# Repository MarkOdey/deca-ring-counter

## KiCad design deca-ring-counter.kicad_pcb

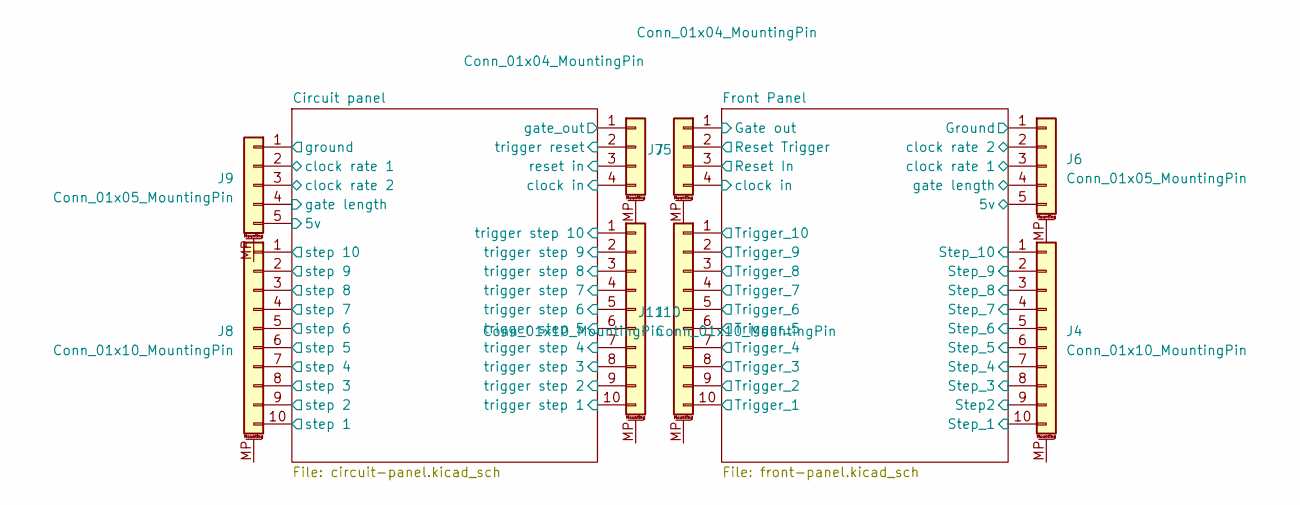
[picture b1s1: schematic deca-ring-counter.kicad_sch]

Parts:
J4, J11: Conn_01x10_MountingPin; PinHeader_1x10_P2.54mm_Vertical
J5: Conn_01x04_MountingPin; PinSocket_1x04_P2.54mm_Vertical
J6: Conn_01x05_MountingPin; PinHeader_1x05_P2.54mm_Vertical
J7: Conn_01x04_MountingPin; PinHeader_1x04_P2.54mm_Vertical
J8, J10: Conn_01x10_MountingPin; PinSocket_1x10_P2.54mm_Vertical
J9: Conn_01x05_MountingPin; PinSocket_1x05_P2.54mm_Vertical

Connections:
+5V: J9.5; also elsewhere on the board
/Circuit panel/clock in: J5.4; also elsewhere on the board
/Circuit panel/clock rate 1: J9.2; also elsewhere on the board
/Circuit panel/clock rate 2: J9.3; also elsewhere on the board
/Circuit panel/gate length: J9.4; also elsewhere on the board
/Circuit panel/gate_out: J5.1; also elsewhere on the board
/Circuit panel/reset in: J5.3; also elsewhere on the board
/Circuit panel/step 1: J8.10; also elsewhere on the board
/Circuit panel/step 2: J8.9; also elsewhere on the board
/Circuit panel/step 3: J8.8; also elsewhere on the board
/Circuit panel/step 4: J8.7; also elsewhere on the board
/Circuit panel/step 5: J8.6; also elsewhere on the board
/Circuit panel/step 6: J8.5; also elsewhere on the board
/Circuit panel/step 7: J8.4; also elsewhere on the board
/Circuit panel/step 8: J8.3; also elsewhere on the board
/Circuit panel/step 9: J8.2; also elsewhere on the board
/Circuit panel/step 10: J8.1; also elsewhere on the board
/Circuit panel/trigger reset: J5.2; also elsewhere on the board
/Circuit panel/trigger step 1: J10.10; also elsewhere on the board
/Circuit panel/trigger step 2: J10.9; also elsewhere on the board
/Circuit panel/trigger step 3: J10.8; also elsewhere on the board
/Circuit panel/trigger step 4: J10.7; also elsewhere on the board
/Circuit panel/trigger step 5: J10.6; also elsewhere on the board
/Circuit panel/trigger step 6: J10.5; also elsewhere on the board
/Circuit panel/trigger step 7: J10.4; also elsewhere on the board
/Circuit panel/trigger step 8: J10.3; also elsewhere on the board
/Circuit panel/trigger step 9: J10.2; also elsewhere on the board
/Circuit panel/trigger step 10: J10.1; also elsewhere on the board
/Front Panel/5v: J6.5; also elsewhere on the board
/Front Panel/Gate out: J7.1; also elsewhere on the board
/Front Panel/Ground: J6.1; also elsewhere on the board
/Front Panel/Reset In: J7.3; also elsewhere on the board
/Front Panel/Reset Trigger: J7.2; also elsewhere on the board
/Front Panel/Step2: J4.9; also elsewhere on the board
/Front Panel/Step_1: J4.10; also elsewhere on the board
/Front Panel/Step_3: J4.8; also elsewhere on the board
/Front Panel/Step_4: J4.7; also elsewhere on the board
/Front Panel/Step_5: J4.6; also elsewhere on the board
/Front Panel/Step_6: J4.5; also elsewhere on the board
/Front Panel/Step_7: J4.4; also elsewhere on the board
/Front Panel/Step_8: J4.3; also elsewhere on the board
/Front Panel/Step_9: J4.2; also elsewhere on the board
/Front Panel/Step_10: J4.1; also elsewhere on the board
/Front Panel/Trigger_1: J11.10; also elsewhere on the board
/Front Panel/Trigger_2: J11.9; also elsewhere on the board
/Front Panel/Trigger_3: J11.8; also elsewhere on the board
/Front Panel/Trigger_4: J11.7; also elsewhere on the board
/Front Panel/Trigger_5: J11.6; also elsewhere on the board
/Front Panel/Trigger_6: J11.5; also elsewhere on the board
/Front Panel/Trigger_7: J11.4; also elsewhere on the board
/Front Panel/Trigger_8: J11.3; also elsewhere on the board
/Front Panel/Trigger_9: J11.2; also elsewhere on the board
/Front Panel/Trigger_10: J11.1; also elsewhere on the board
/Front Panel/clock in: J7.4; also elsewhere on the board
/Front Panel/clock rate 1: J6.3; also elsewhere on the board
/Front Panel/clock rate 2: J6.2; also elsewhere on the board
/Front Panel/gate length: J6.4; also elsewhere on the board
GND: J9.1; also elsewhere on the board

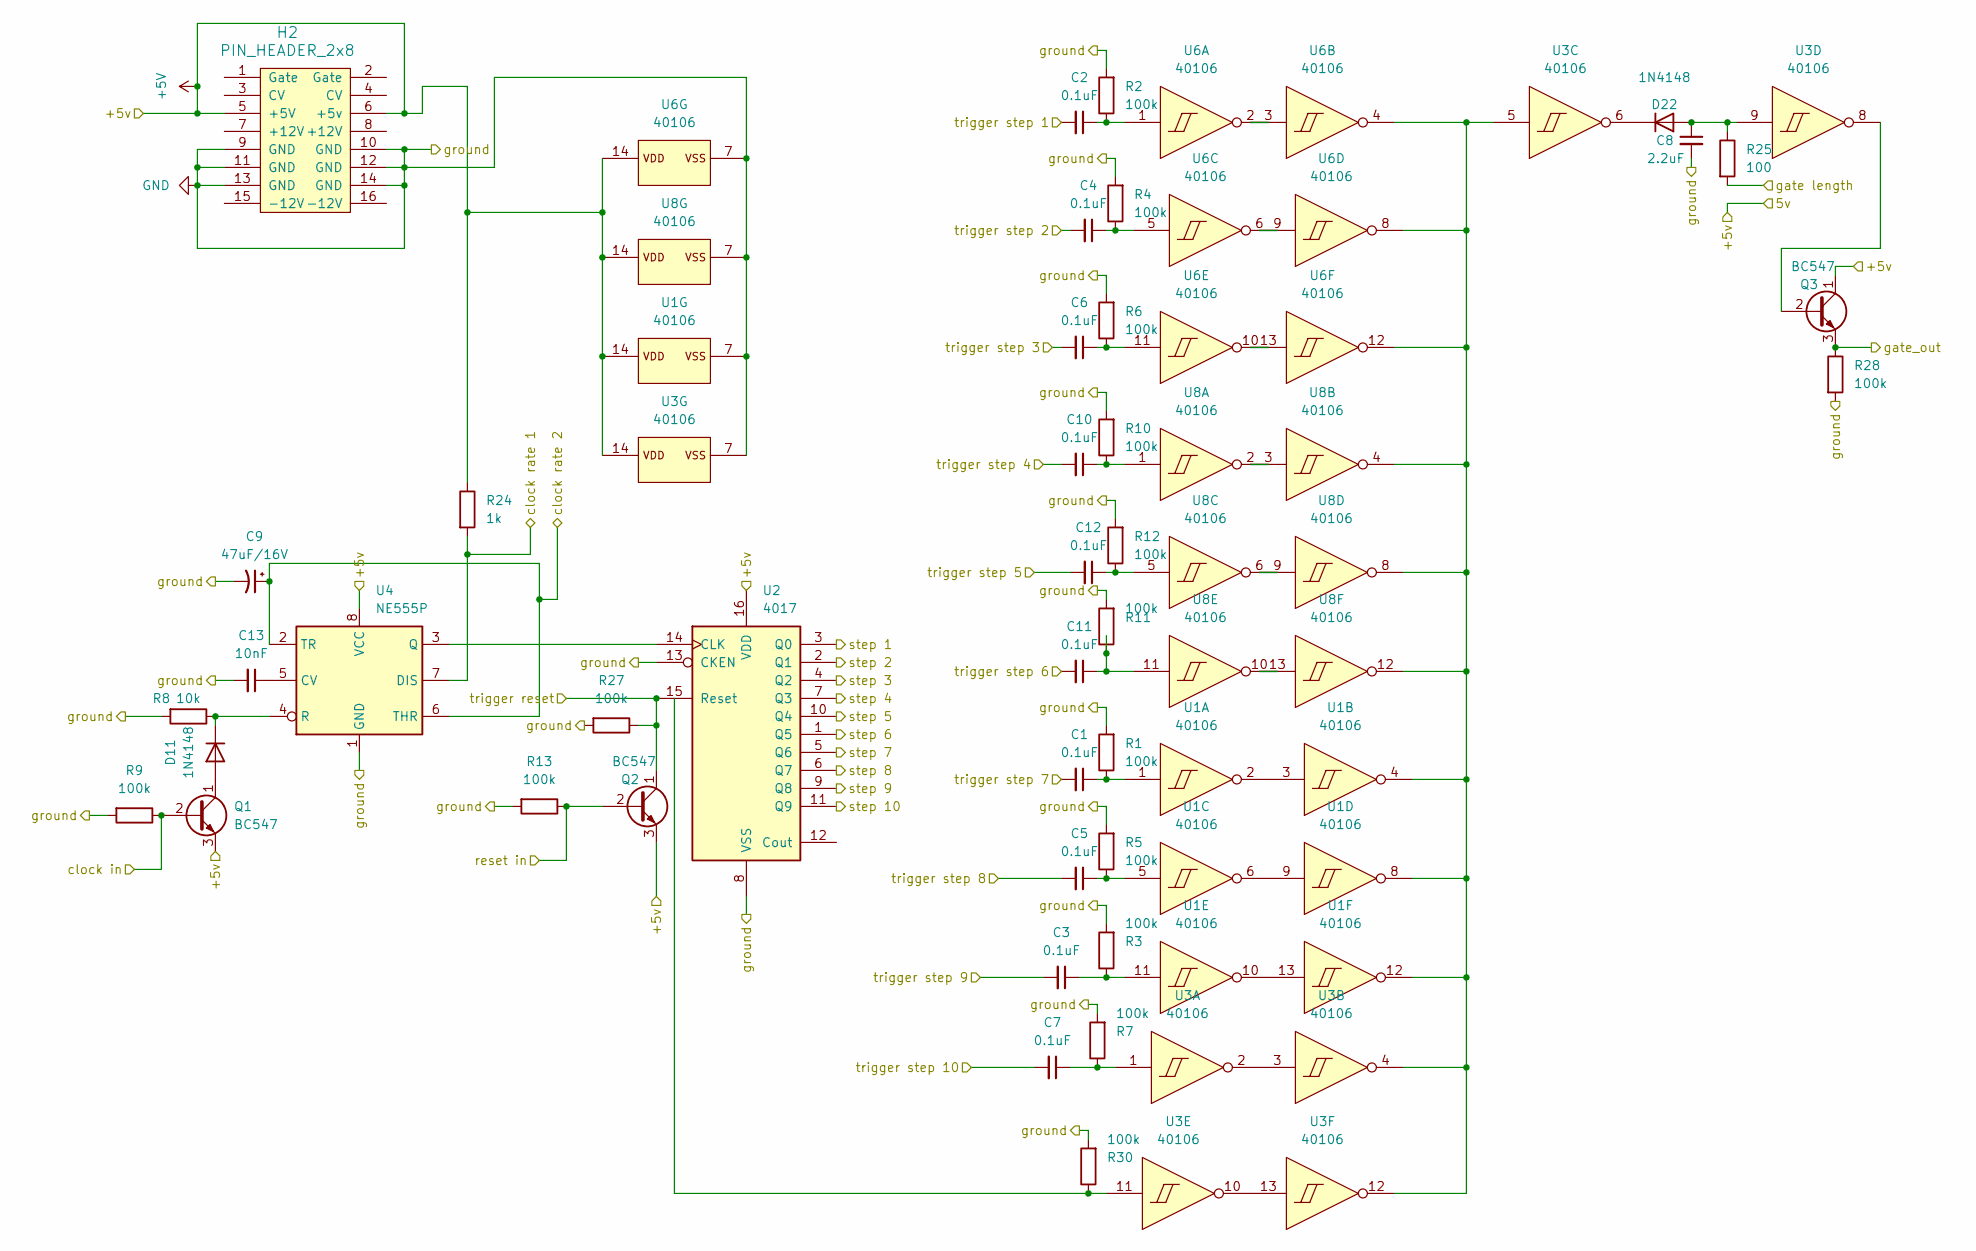
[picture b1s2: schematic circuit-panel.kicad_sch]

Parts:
C1, C2, C3, C4, C5, C6, C7, C10, C11, C12: 0.1uF_0603_16V; C_Disc_D3.8mm_W2.6mm_P2.50mm; Part Number 0603YC104KAT2A; JLCPCB ID C14663
C8: 2.2uF_0603_25V; C_Disc_D3.8mm_W2.6mm_P2.50mm; Part Number GRM188R6YA225KA12D; JLCPCB ID C57895
C9: 47uF_5x5.3_16V; CP_Radial_D7.5mm_P2.50mm; Part Number VE-470M1CTR-0505; JLCPCB ID C134798
C13: 10nF_0603_25V; C_Disc_D3.8mm_W2.6mm_P2.50mm; Part Number 06035C103KAT2A; JLCPCB ID C57112
D11, D22: 1N4148; D_DO-35_SOD27_P7.62mm_Horizontal
H2: PIN_HEADER_2x8; Pins_2x08_2.54mm_TH_EuroPower_Shrouded
Q1, Q2, Q3: BC547; TO-92_Inline
R1, R2, R3, R4, R5, R6, R7, R9, R10, R11, R12, R13, R27, R30: 100k_0603; R_Axial_DIN0207_L6.3mm_D2.5mm_P7.62mm_Horizontal; Part Number RC0603FR-07100KL; JLCPCB ID C25803
R8, R24, R25, R28: 10k_0603; R_Axial_DIN0207_L6.3mm_D2.5mm_P7.62mm_Horizontal; Part Number RC0603FR-0710KL; JLCPCB ID C25804
U1, U3, U6, U8: CD40106BPWR; DIP-14_W7.62mm_LongPads; Part Number CD40106BPWR; JLCPCB ID C58834
U2: 4017; DIP-16_W7.62mm_LongPads
U4: NE555P; DIP-8_W7.62mm

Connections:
+5V: H2.5 (+5V), H2.6 (+5v), Q1.3 (E), Q2.3 (E), Q3.1 (C), R24.1, U1.14 (VDD), U2.16 (VDD), U3.14 (VDD), U4.8 (VCC), U6.14 (VDD), U8.14 (VDD); also elsewhere on the board
/Circuit panel/clock in: Q1.2 (B), R9.1; also elsewhere on the board
/Circuit panel/clock rate 1: R24.2, U4.7 (DIS); also elsewhere on the board
/Circuit panel/clock rate 2: C9.1, U4.2 (TR), U4.6 (THR); also elsewhere on the board
/Circuit panel/gate length: R25.2; also elsewhere on the board
/Circuit panel/gate_out: Q3.3 (E), R28.1; also elsewhere on the board
/Circuit panel/reset in: Q2.2 (B), R13.1; also elsewhere on the board
/Circuit panel/step 1: U2.3 (Q0); also elsewhere on the board
/Circuit panel/step 2: U2.2 (Q1); also elsewhere on the board
/Circuit panel/step 3: U2.4 (Q2); also elsewhere on the board
/Circuit panel/step 4: U2.7 (Q3); also elsewhere on the board
/Circuit panel/step 5: U2.10 (Q4); also elsewhere on the board
/Circuit panel/step 6: U2.1 (Q5); also elsewhere on the board
/Circuit panel/step 7: U2.5 (Q6); also elsewhere on the board
/Circuit panel/step 8: U2.6 (Q7); also elsewhere on the board
/Circuit panel/step 9: U2.9 (Q8); also elsewhere on the board
/Circuit panel/step 10: U2.11 (Q9); also elsewhere on the board
/Circuit panel/trigger reset: Q2.1 (C), R27.1, U2.15 (Reset); also elsewhere on the board
/Circuit panel/trigger step 1: C2.2; also elsewhere on the board
/Circuit panel/trigger step 2: C4.2; also elsewhere on the board
/Circuit panel/trigger step 3: C6.2; also elsewhere on the board
/Circuit panel/trigger step 4: C10.2; also elsewhere on the board
/Circuit panel/trigger step 5: C12.2; also elsewhere on the board
/Circuit panel/trigger step 6: C11.2; also elsewhere on the board
/Circuit panel/trigger step 7: C1.2; also elsewhere on the board
/Circuit panel/trigger step 8: C5.2; also elsewhere on the board
/Circuit panel/trigger step 9: C3.2; also elsewhere on the board
/Circuit panel/trigger step 10: C7.2; also elsewhere on the board
GND: C8.2, C9.2, C13.2, H2.9 (GND), H2.10 (GND), H2.11 (GND), H2.12 (GND), H2.13 (GND), H2.14 (GND), R1.2, R2.2, R3.2, R4.2, R5.2, R6.2, R7.2, R8.2, R9.2, R10.2, R11.2, R12.2, R13.2, R27.2, R28.2, R30.2, U1.7 (VSS), U2.8 (VSS), U2.13 (CKEN), U3.7 (VSS), U4.1 (GND), U6.7 (VSS), U8.7 (VSS); also elsewhere on the board
unnamed: D11.2 (A), Q1.1 (C)
unnamed: D11.1 (K), R8.1, U4.4 (R)
unnamed: C8.1, D22.2 (A), R25.1, U3.9 (I)
unnamed: D22.1 (K), U3.6 (O)
unnamed: Q3.2 (B), U3.8 (O)
unnamed: C1.1, R1.1, U1.1 (I)
unnamed: U1.2 (O), U1.3 (I)
unnamed: U1.4 (O), U1.8 (O), U1.12 (O), U3.4 (O), U3.5 (I), U3.12 (O), U6.4 (O), U6.8 (O), U6.12 (O), U8.4 (O), U8.8 (O), U8.12 (O)
unnamed: C5.1, R5.1, U1.5 (I)
unnamed: U1.6 (O), U1.9 (I)
unnamed: C3.1, R3.1, U1.11 (I)
unnamed: U1.10 (O), U1.13 (I)
unnamed: U2.14 (CLK), U4.3 (Q)
unnamed: C7.1, R7.1, U3.1 (I)
unnamed: U3.2 (O), U3.3 (I)
unnamed: R30.1, U3.11 (I)
unnamed: U3.10 (O), U3.13 (I)
unnamed: C13.1, U4.5 (CV)
unnamed: C2.1, R2.1, U6.1 (I)
unnamed: U6.2 (O), U6.3 (I)
unnamed: C4.1, R4.1, U6.5 (I)
unnamed: U6.6 (O), U6.9 (I)
unnamed: C6.1, R6.1, U6.11 (I)
unnamed: U6.10 (O), U6.13 (I)
unnamed: C10.1, R10.1, U8.1 (I)
unnamed: U8.2 (O), U8.3 (I)
unnamed: C12.1, R12.1, U8.5 (I)
unnamed: U8.6 (O), U8.9 (I)
unnamed: C11.1, R11.1, U8.11 (I)
unnamed: U8.10 (O), U8.13 (I)

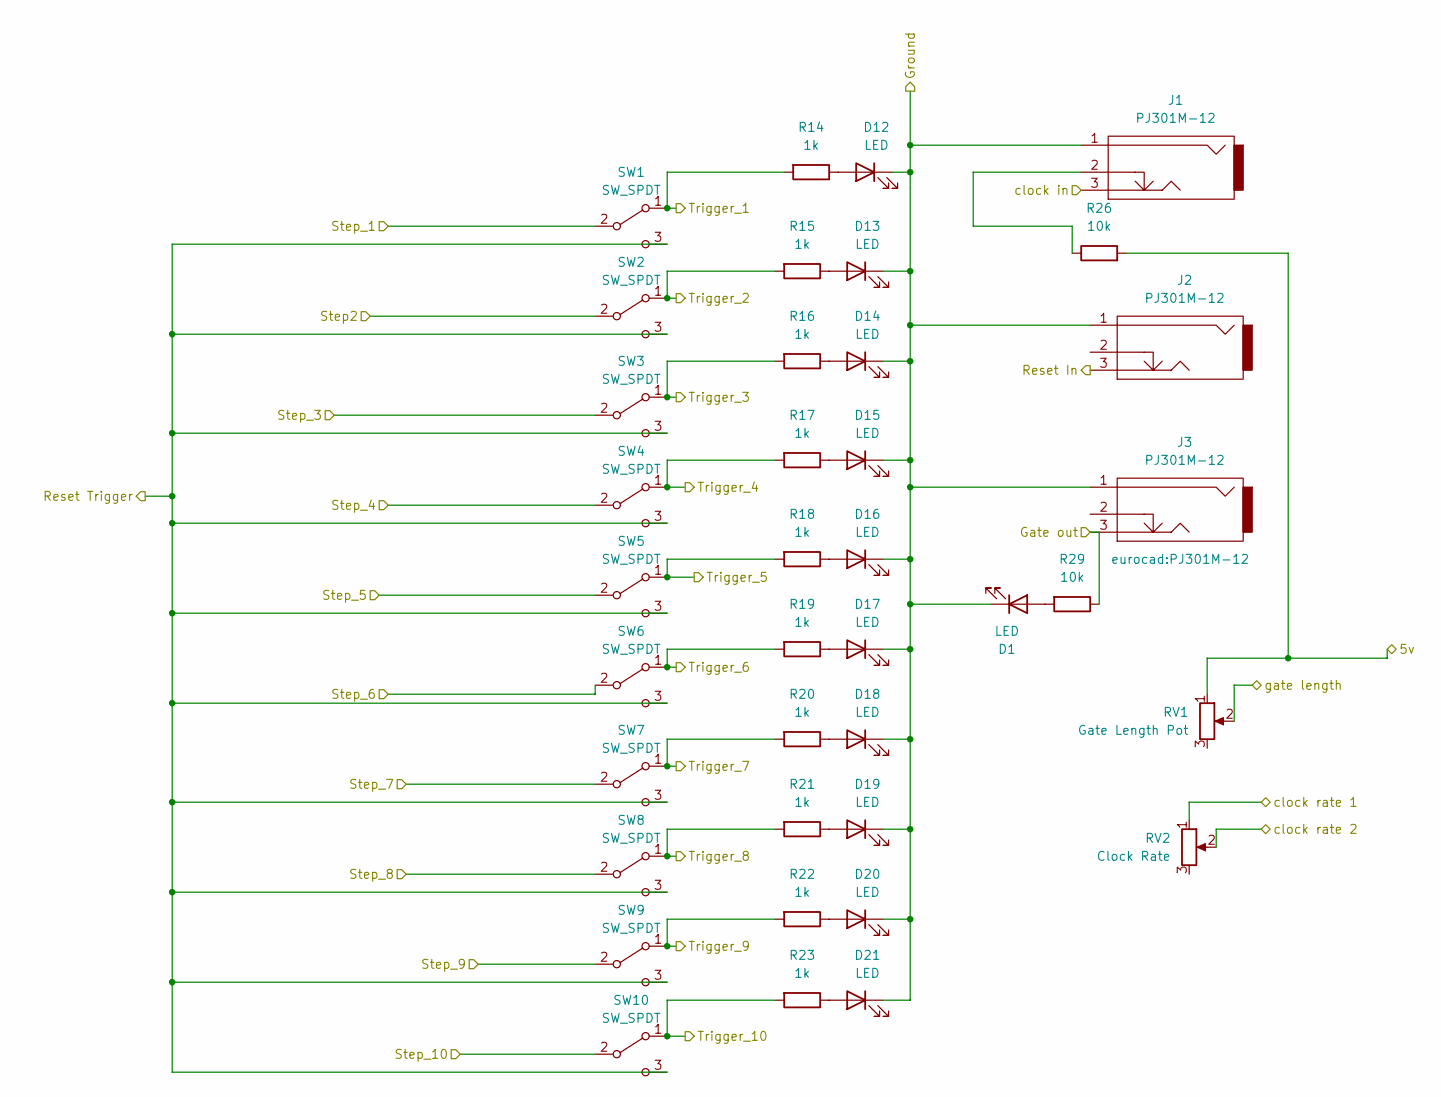
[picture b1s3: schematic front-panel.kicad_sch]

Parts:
D1, D12, D13, D14, D15, D16, D17, D18, D19, D20, D21: LED; LED3mm
J1, J2, J3: PJ301M-12
R14, R15, R16, R17, R18, R19, R20, R21, R22, R23, R29: 1k_0603; R_Axial_DIN0207_L6.3mm_D2.5mm_P7.62mm_Horizontal; Part Number RC0603FR-071KL; JLCPCB ID C21190
R26: 10k_0603; R_Axial_DIN0207_L6.3mm_D2.5mm_P7.62mm_Horizontal; Part Number RC0603FR-0710KL; JLCPCB ID C25804
RV1: Gate Length Pot; Pot_9mm_Knurl_NoDet
RV2: Clock Rate; Pot_9mm_Knurl_NoDet
SW1, SW2, SW3, SW4, SW5, SW6, SW7, SW8, SW9, SW10: SW_SPDT; Switch_Toggle_SPDT_Mini_SolderLug

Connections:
/Front Panel/5v: R26.2, RV1.1; also elsewhere on the board
/Front Panel/Gate out: J3.3, R29.1; also elsewhere on the board
/Front Panel/Ground: D1.1 (K), D12.1 (K), D13.1 (K), D14.1 (K), D15.1 (K), D16.1 (K), D17.1 (K), D18.1 (K), D19.1 (K), D20.1 (K), D21.1 (K), J1.1, J2.1, J3.1; also elsewhere on the board
/Front Panel/Reset In: J2.3; also elsewhere on the board
/Front Panel/Reset Trigger: SW1.3 (C), SW2.3 (C), SW3.3 (C), SW4.3 (C), SW5.3 (C), SW6.3 (C), SW7.3 (C), SW8.3 (C), SW9.3 (C), SW10.3 (C); also elsewhere on the board
/Front Panel/Step2: SW2.2 (B); also elsewhere on the board
/Front Panel/Step_1: SW1.2 (B); also elsewhere on the board
/Front Panel/Step_3: SW3.2 (B); also elsewhere on the board
/Front Panel/Step_4: SW4.2 (B); also elsewhere on the board
/Front Panel/Step_5: SW5.2 (B); also elsewhere on the board
/Front Panel/Step_6: SW6.2 (B); also elsewhere on the board
/Front Panel/Step_7: SW7.2 (B); also elsewhere on the board
/Front Panel/Step_8: SW8.2 (B); also elsewhere on the board
/Front Panel/Step_9: SW9.2 (B); also elsewhere on the board
/Front Panel/Step_10: SW10.2 (B); also elsewhere on the board
/Front Panel/Trigger_1: R14.2, SW1.1 (A); also elsewhere on the board
/Front Panel/Trigger_2: R15.2, SW2.1 (A); also elsewhere on the board
/Front Panel/Trigger_3: R16.2, SW3.1 (A); also elsewhere on the board
/Front Panel/Trigger_4: R17.2, SW4.1 (A); also elsewhere on the board
/Front Panel/Trigger_5: R18.2, SW5.1 (A); also elsewhere on the board
/Front Panel/Trigger_6: R19.2, SW6.1 (A); also elsewhere on the board
/Front Panel/Trigger_7: R20.2, SW7.1 (A); also elsewhere on the board
/Front Panel/Trigger_8: R21.2, SW8.1 (A); also elsewhere on the board
/Front Panel/Trigger_9: R22.2, SW9.1 (A); also elsewhere on the board
/Front Panel/Trigger_10: R23.2, SW10.1 (A); also elsewhere on the board
/Front Panel/clock in: J1.3; also elsewhere on the board
/Front Panel/clock rate 1: RV2.1; also elsewhere on the board
/Front Panel/clock rate 2: RV2.2; also elsewhere on the board
/Front Panel/gate length: RV1.2; also elsewhere on the board
unnamed: D1.2 (A), R29.2
unnamed: D12.2 (A), R14.1
unnamed: D13.2 (A), R15.1
unnamed: D14.2 (A), R16.1
unnamed: D15.2 (A), R17.1
unnamed: D16.2 (A), R18.1
unnamed: D17.2 (A), R19.1
unnamed: D18.2 (A), R20.1
unnamed: D19.2 (A), R21.1
unnamed: D20.2 (A), R22.1
unnamed: D21.2 (A), R23.1
unnamed: J1.2, R26.1

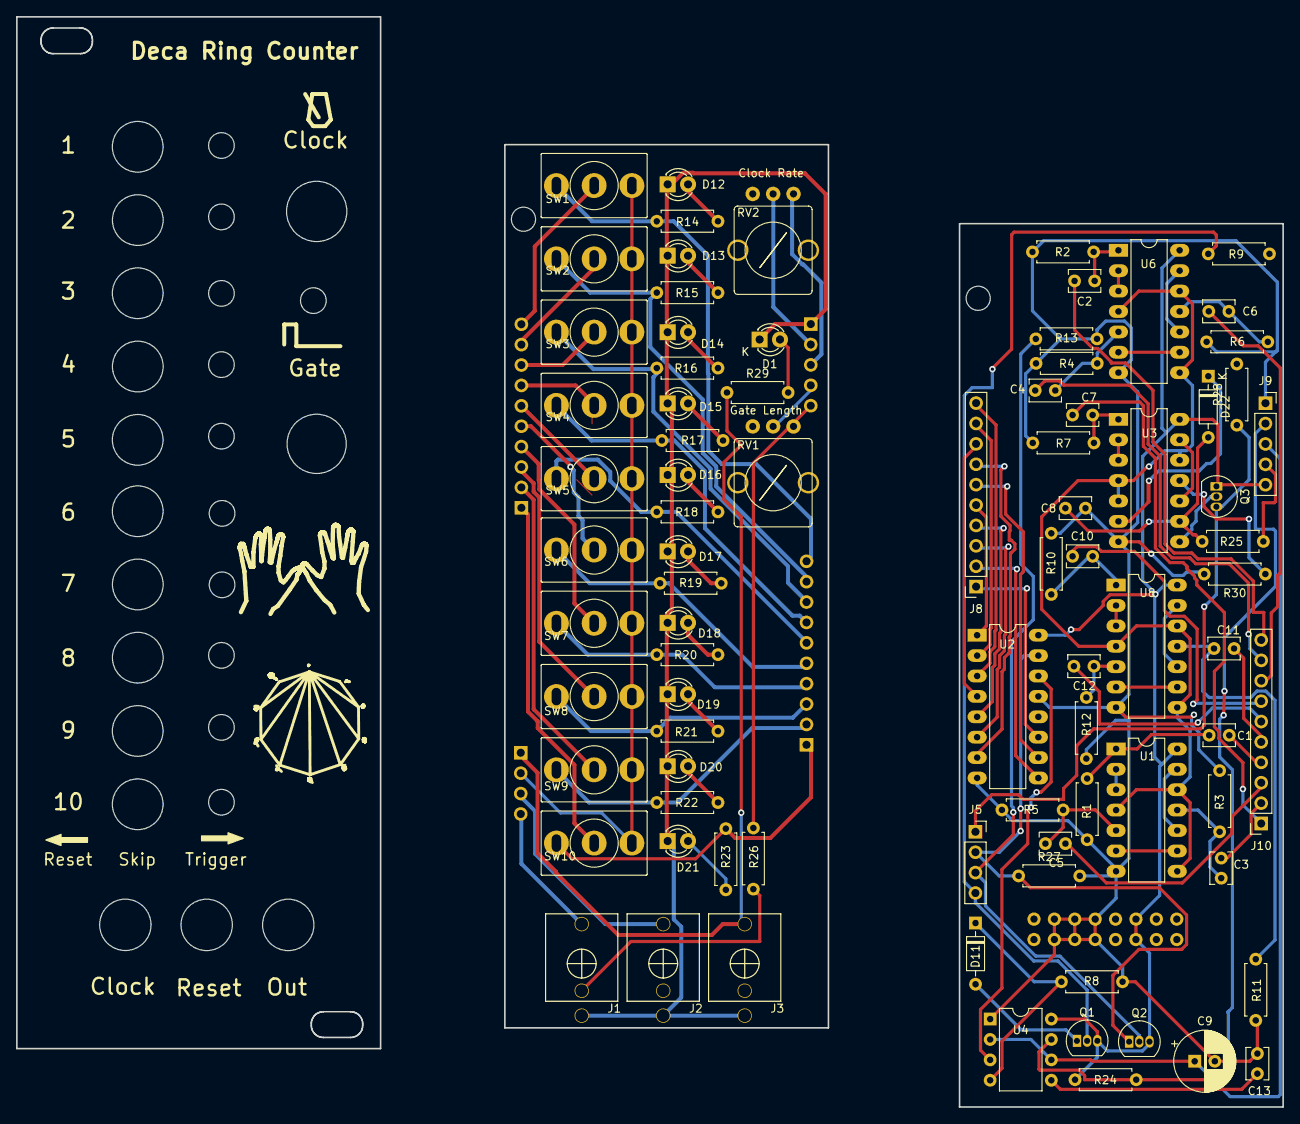
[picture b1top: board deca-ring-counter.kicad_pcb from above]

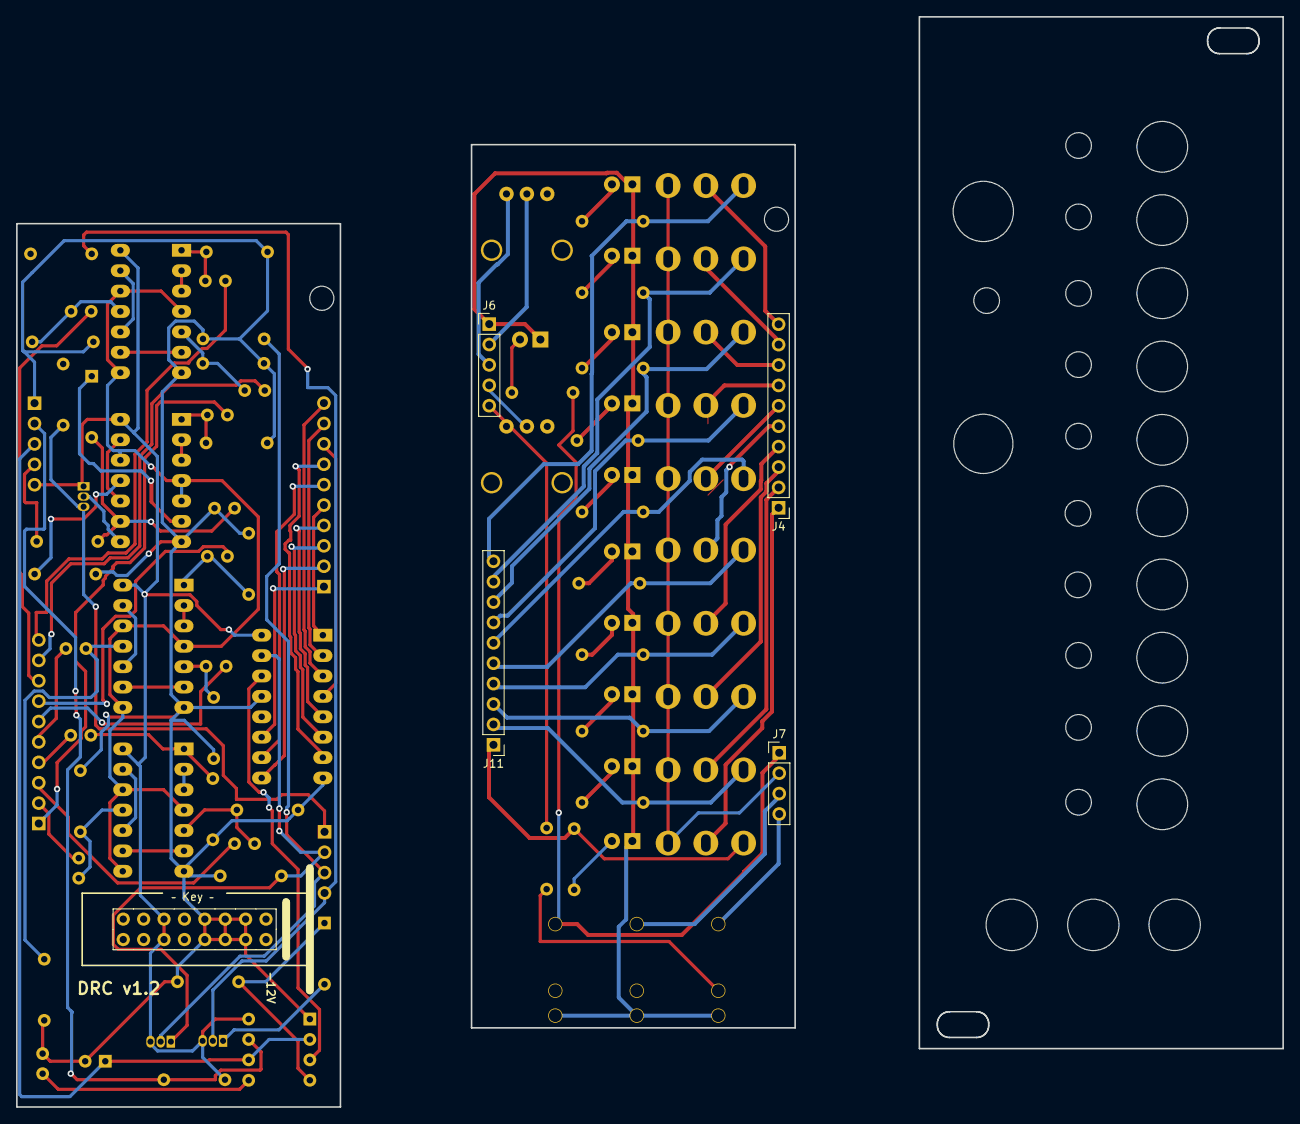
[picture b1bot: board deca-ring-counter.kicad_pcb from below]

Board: 2 copper layers, 157.7 x 135.8 mm, 89 parts (5 on the bottom side), 100 nets.

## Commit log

2024-02-03 locked version 1..2
2024-02-11 Fixed critical routing bugs
2024-04-01 Version 1.3 of the model.
2024-04-01 Added readme file.
2024-04-01 Renamed md file.
